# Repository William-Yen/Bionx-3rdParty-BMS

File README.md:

# Bionx-3rdParty-BMS
A supplemental PCB to retrofit a Bionx e-bike battery pack with a 3rd-party BMS

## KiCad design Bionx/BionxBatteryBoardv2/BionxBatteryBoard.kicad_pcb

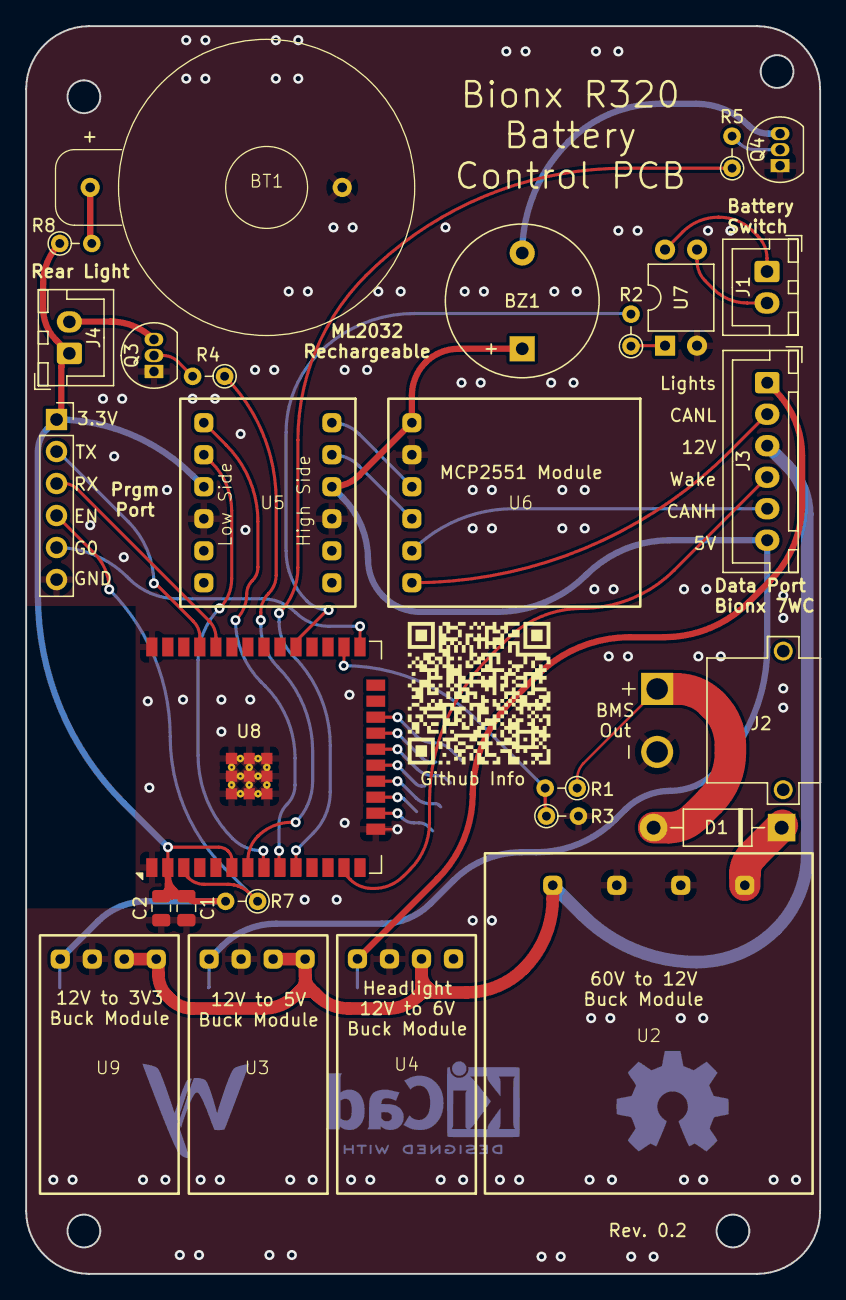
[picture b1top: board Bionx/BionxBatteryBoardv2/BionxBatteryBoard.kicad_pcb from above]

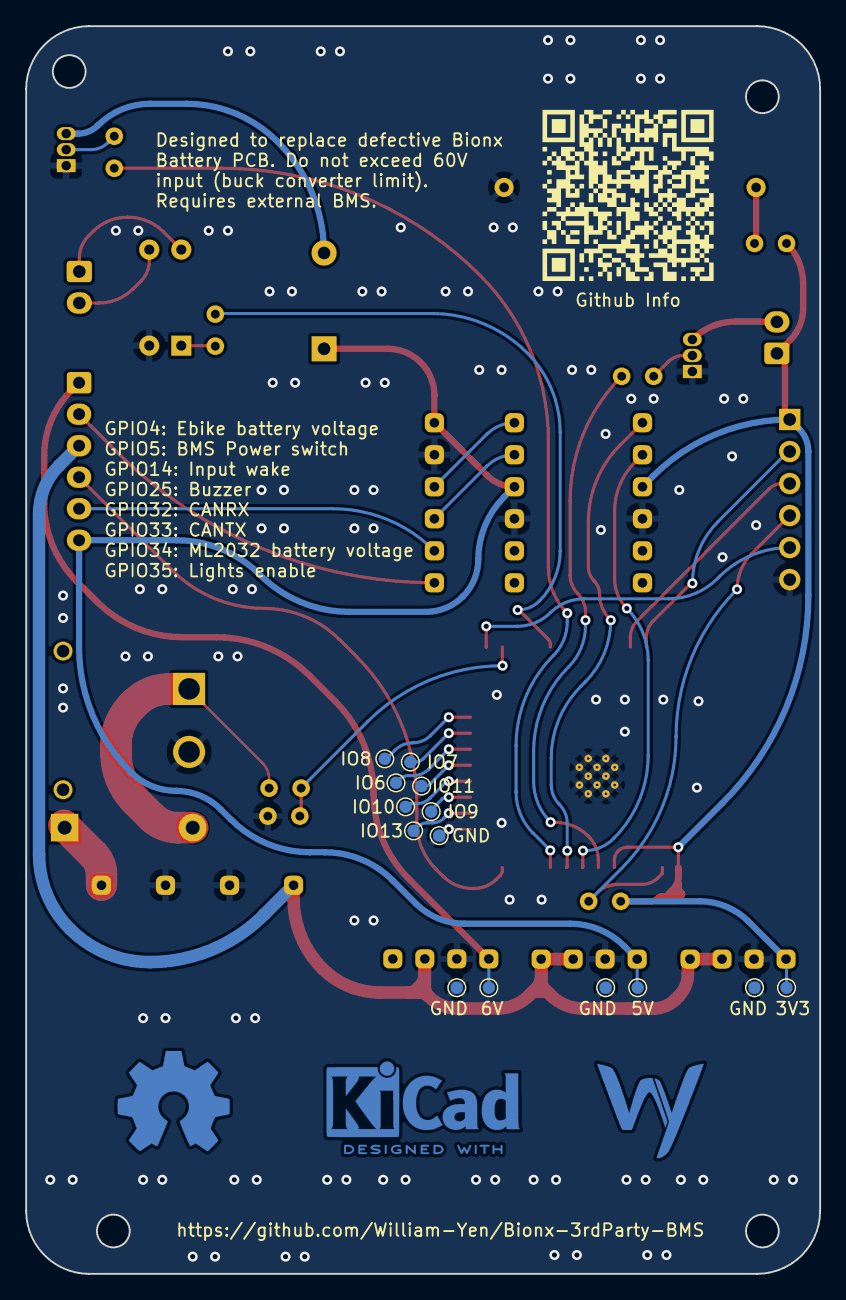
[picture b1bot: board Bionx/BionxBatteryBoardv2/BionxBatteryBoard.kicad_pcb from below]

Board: 2 copper layers, 63.0 x 99.0 mm, 41 parts (14 on the bottom side), 30 nets.

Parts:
3V3, 5V, 6V: TestPoint_Pad_D1.0mm
BT1: Battery_Cell; 2032_THT
BZ1: Buzzer; Buzzer_12x9.5RM7.6
C1: 10uF; C_0805_2012Metric
C2: 100nF; C_0805_2012Metric
D1: D; D_DO-41_SOD81_P10.16mm_Horizontal
GND: TestPoint_Pad_D1.0mm
GND#2, GND#3, GND#4: TestPoint_Pad_D1.0mm
IO6, IO7, IO8, IO9, IO10, IO11, IO13: TestPoint_Pad_D1.0mm
J1, J4: Conn_01x02; JST_XH_B2B-XH-A_1x02_P2.50mm_Vertical
J2: XT30PW-M; AMASS_XT30PW-M
J3: Conn_01x06; JST_XH_B6B-XH-A_1x06_P2.50mm_Vertical
J5: Conn_01x06; PinSocket_1x06_P2.54mm_Vertical
Q3, Q4: 2N3904; TO-92_Inline
R1: 100k; R_Axial_DIN0204_L3.6mm_D1.6mm_P2.54mm_Vertical
R2: 184R; R_Axial_DIN0204_L3.6mm_D1.6mm_P2.54mm_Vertical
R3: 5.1k; R_Axial_DIN0204_L3.6mm_D1.6mm_P2.54mm_Vertical
R4, R5: 220R; R_Axial_DIN0204_L3.6mm_D1.6mm_P2.54mm_Vertical
R7: 10k; R_Axial_DIN0204_L3.6mm_D1.6mm_P2.54mm_Vertical
R8: 680R; R_Axial_DIN0204_L3.6mm_D1.6mm_P2.54mm_Vertical
U2: CR-6030S_Buck_Converter; CR-6030S Buck Module
U3, U4, U9: Adj_Buck_Module; Adj Buck Module
U5: 4-channel_LevelShifter; Logic Level Converter Module
U6: MCP2551_Module; MCP2551 Module
U7: PC817; DIP-4_W7.62mm
U8: ESP32-WROOM-32D; ESP32-WROOM-32E

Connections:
+3.3V: 3V3.1, C1.1, C2.1, J4.1, J5.1, R7.2, R8.1, U5.9 (LV), U8.2 (VDD), U8.6 (IO34), U9.4 (OUT+)
+5V: 5V.1, BZ1.1 (+), J3.6, U3.4 (OUT+), U5.3 (HV), U6.1 (VCC)
+12V: J3.3, U2.4 (OUT+), U3.1 (EN), U3.2 (IN+), U4.2 (IN+), U9.1 (EN), U9.2 (IN+)
+BATT: D1.2 (A), J2.P, R1.1
-BATT: BT1.2 (-), C1.2, C2.2, GND.1, GND#2.1, GND#3.1, GND#4.1, J2.N, J5.6, Q3.1 (E), Q4.1 (E), R3.2, U2.2 (GND), U2.3 (GND), U3.3 (GND), U4.3 (GND), U5.4 (GND), U5.10 (GND), U6.2 (GND), U7.2, U8.1 (GND), U8.15 (GND), U8.38 (GND), U8.39 (GND), U9.3 (GND)
/CAN_H: J3.5, U6.5 (CANH)
/CAN_L: J3.2, U6.6 (CANL)
/CAN_RX: U5.8 (LV2), U8.8 (IO32)
/CAN_TX: U5.7 (LV1), U8.9 (IO33)
/EN: J5.4, R7.1, U8.3 (EN)
/IO0: J5.5, U8.25 (IO0)
/LightsEnable_pin: R4.1, U8.7 (IO35)
/PowerSwitch_pin: R2.2, U8.29 (IO5)
/RX0: J5.3, U8.34 (RXD0/IO3)
/Ride+_Wakepin: J3.4, U8.13 (IO14)
/TX0: J5.2, U8.35 (TXD0/IO1)
/batteryRead_pin: R1.2, R3.1, U8.26 (IO4)
/buzzer_pin: R5.1, U8.10 (IO25)
Headlight_power: 6V.1, J3.1, U4.4 (OUT+)
unnamed: BT1.1 (+), R8.2
unnamed: BZ1.2 (-), Q4.3 (C)
unnamed: D1.1 (K), U2.1 (IN+)
unnamed: J1.1, U7.4
unnamed: J1.2, U7.3
unnamed: J4.2, Q3.3 (C)
unnamed: Q3.2 (B), R4.2
unnamed: Q4.2 (B), R5.2
unnamed: R2.1, U7.1
unnamed: U5.1 (HV1), U6.3 (CTX)
unnamed: U5.2 (HV2), U6.4 (CRX)

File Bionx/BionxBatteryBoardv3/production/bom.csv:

Designator,Footprint,Quantity,Value,LCSC Part #
BT1,2032_THT,1,Battery_Cell,
BZ1,Buzzer_12x9.5RM7.6,1,Buzzer,
C1,0805,1,10uF,
C2,0805,1,100nF,
D1,D_DO-41_SOD81_P10.16mm_Horizontal,1,D,
"J1, J4",JST_XH_B2B-XH-A_1x02_P2.50mm_Vertical,2,Conn_01x02,
J2,AMASS_XT30PW-M,1,XT30PW-M,
J3,JST_XH_B6B-XH-A_1x06_P2.50mm_Vertical,1,Conn_01x06,
J5,PinSocket_1x06_P2.54mm_Vertical,1,Conn_01x06,
"Q3, Q4",TO-92_Inline,2,2N3904,
R1,R_Axial_DIN0204_L3.6mm_D1.6mm_P2.54mm_Vertical,1,100k,
R2,R_Axial_DIN0204_L3.6mm_D1.6mm_P2.54mm_Vertical,1,184R,
R3,R_Axial_DIN0204_L3.6mm_D1.6mm_P2.54mm_Vertical,1,5.1k,
"R4, R5",R_Axial_DIN0204_L3.6mm_D1.6mm_P2.54mm_Vertical,2,220R,
R7,R_Axial_DIN0204_L3.6mm_D1.6mm_P2.54mm_Vertical,1,10k,
R8,R_Axial_DIN0204_L3.6mm_D1.6mm_P2.54mm_Vertical,1,680R,
U2,CR-6030S Buck Module,1,CR-6030S_Buck_Converter,
"U3, U4, U9",Adj Buck Module,3,Adj_Buck_Module,
U5,Logic Level Converter Module,1,4-channel_LevelShifter,
U6,MCP2551 Module,1,MCP2551_Module,
U7,DIP-4_W7.62mm,1,PC817,
U8,ESP32-WROOM-32E,1,ESP32-WROOM-32D,

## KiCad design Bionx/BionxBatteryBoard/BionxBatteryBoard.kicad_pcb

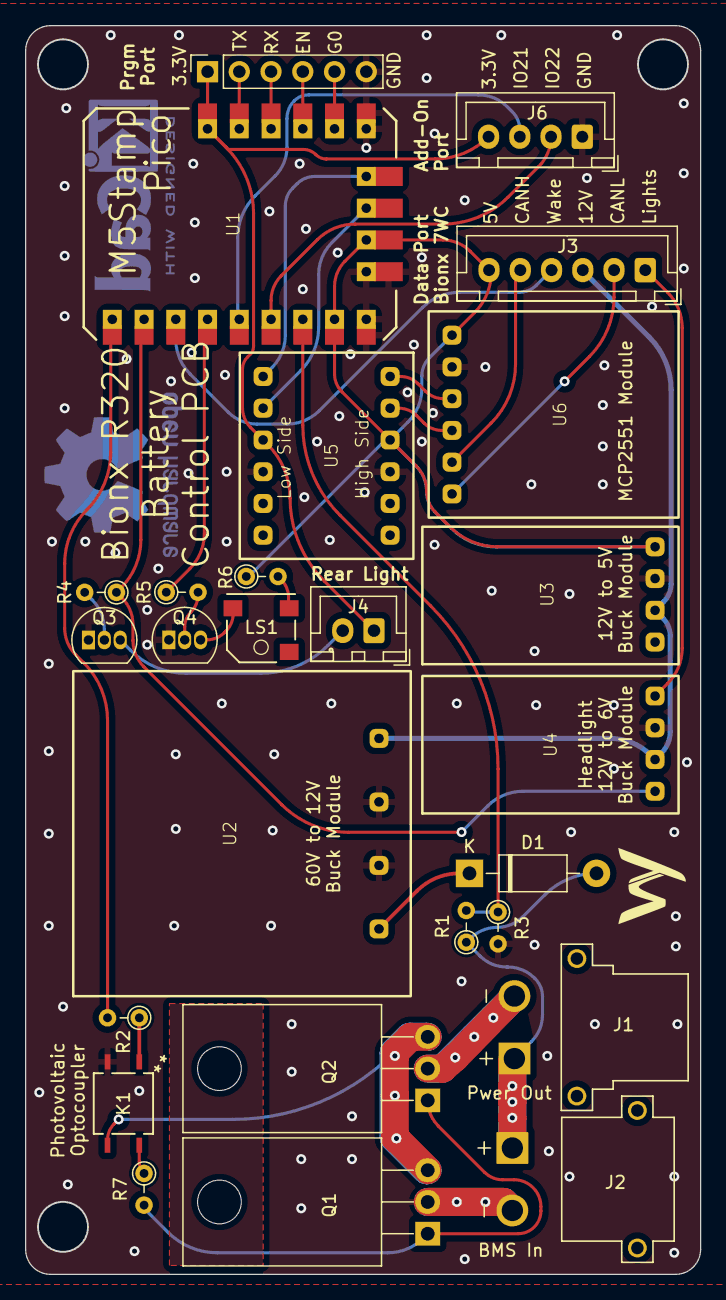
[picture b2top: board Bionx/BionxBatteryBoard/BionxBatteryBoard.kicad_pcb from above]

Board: 2 copper layers, 53.9 x 99.9 mm, 26 parts (0 on the bottom side), 34 nets.

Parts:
D1: D; D_DO-41_SOD81_P10.16mm_Horizontal
J1: XT30PW-F; AMASS_XT30PW-F
J2: XT30PW-M; AMASS_XT30PW-M
J3: Conn_01x06_Socket; JST_XH_B6B-XH-A_1x06_P2.50mm_Vertical
J4: Conn_01x02_Socket; JST_XH_B2B-XH-A_1x02_P2.50mm_Vertical
J5: Conn_01x06_Pin; PinSocket_1x06_P2.54mm_Vertical
J6: Conn_01x04_Socket; JST_XH_B4B-XH-A_1x04_P2.50mm_Vertical
K1: APV1121S; SOP4PIN_PAN
LS1: CMT-0502-75-SMT-TR; CMT-0502_CUD
Q1, Q2: STB75NF75LT4; TO-220-3_Horizontal_TabDown
Q3, Q4: 2N3904; TO-92_Inline
R1, R2, R3, R4, R5, R6, R7: R; R_Axial_DIN0204_L3.6mm_D1.6mm_P2.54mm_Vertical
U1: M5Stack-STAMP-PICO; M5Stamp Pico
U2: CR-6030S_Buck_Converter; CR-6030S Buck Module
U3, U4: Adj_Buck_Module; Adj Buck Module
U5: 4-channel_LevelShifter; Logic Level Converter Module
U6: MCP2551_Module; MCP2551 Module

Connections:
+3.3V: J4.1, J5.1, J6.4, U1.19 (3V3), U5.9 (LV)
+5V: J3.6, R6.1, U1.8 (5V), U1.11 (5V), U3.4 (OUT+), U5.3 (HV), U6.1 (VCC)
+12V: J3.3, U2.4 (OUT+), U3.2 (IN+), U4.2 (IN+)
+BATT: D1.2 (A), J1.P, J2.P, R1.1
-BATT: J2.N, J5.6, J6.1, K1.2, Q1.2 (D), Q3.1 (E), Q4.1 (E), R3.2, U1.9 (GND), U1.10 (GND), U1.14 (GND), U2.2 (GND), U2.3 (GND), U3.3 (GND), U4.3 (GND), U5.4 (GND), U5.10 (GND), U6.2 (GND)
-OUT: J1.N, Q2.2 (D)
/BMS_RX: J6.2, U1.6 (G22)
/BMS_TX: J6.3, U1.5 (G21)
/CAN_H: J3.5, U6.5 (CANH)
/CAN_L: J3.2, U6.6 (CANL)
/CAN_RX: U1.12 (G32), U5.8 (LV2)
/CAN_TX: U1.13 (G33), U5.7 (LV1)
/Headlight_power: J3.1, U4.4 (OUT+)
/LightsEnable_pin: R4.1, U1.2 (G36), U4.1 (EN)
/PowerSwitch_pin: R2.2, U1.1 (G26)
/Ride+_Wakepin: J3.4, U1.3 (G18)
/batteryRead_pin: R1.2, R3.1, U1.7 (G25)
/buzzer_pin: R5.1, U1.4 (G19)
Drain: K1.3, Q1.3 (S), Q2.3 (S)
unnamed: D1.1 (K), U2.1 (IN+)
unnamed: J4.2, Q3.3 (C)
unnamed: J5.2, U1.18 (G1/Tx0)
unnamed: J5.3, U1.17 (G3/Rx0)
unnamed: J5.4, U1.16 (EN)
unnamed: J5.5, U1.15 (G0)
unnamed: K1.1, R2.1
unnamed: K1.4, R7.1
unnamed: LS1.1 (+), R6.2
unnamed: LS1.2 (-), Q4.3 (C)
unnamed: Q1.1 (G), Q2.1 (G), R7.2
unnamed: Q3.2 (B), R4.2
unnamed: Q4.2 (B), R5.2
unnamed: U5.1 (HV1), U6.3 (CTX)
unnamed: U5.2 (HV2), U6.4 (CRX)

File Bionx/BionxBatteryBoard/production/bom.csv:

Designator,Footprint,Quantity,Value,LCSC Part #
D1,D_DO-41_SOD81_P10.16mm_Horizontal,1,D,
J1,AMASS_XT30PW-F,1,XT30PW-F,
J2,AMASS_XT30PW-M,1,XT30PW-M,
J3,JST_XH_B6B-XH-A_1x06_P2.50mm_Vertical,1,Conn_01x06_Socket,
J4,JST_XH_B2B-XH-A_1x02_P2.50mm_Vertical,1,Conn_01x02_Socket,
J5,PinSocket_1x06_P2.54mm_Vertical,1,Conn_01x06_Pin,
J6,JST_XH_B4B-XH-A_1x04_P2.50mm_Vertical,1,Conn_01x04_Socket,
K1,SOP4PIN_PAN,1,APV1121S,
LS1,CMT-0502_CUD,1,CMT-0502-75-SMT-TR,
"Q1, Q2",TO-220-3_Horizontal_TabDown,2,STB75NF75LT4,
"Q3, Q4",TO-92_Inline,2,2N3904,
"R1, R2, R3, R4, R5, R6, R7",R_Axial_DIN0204_L3.6mm_D1.6mm_P2.54mm_Vertical,7,R,
U1,M5Stamp Pico,1,M5Stack-STAMP-PICO,
U2,CR-6030S Buck Module,1,CR-6030S_Buck_Converter,
"U3, U4",Adj Buck Module,2,Adj_Buck_Module,
U5,Logic Level Converter Module,1,4-channel_LevelShifter,
U6,MCP2551 Module,1,MCP2551_Module,

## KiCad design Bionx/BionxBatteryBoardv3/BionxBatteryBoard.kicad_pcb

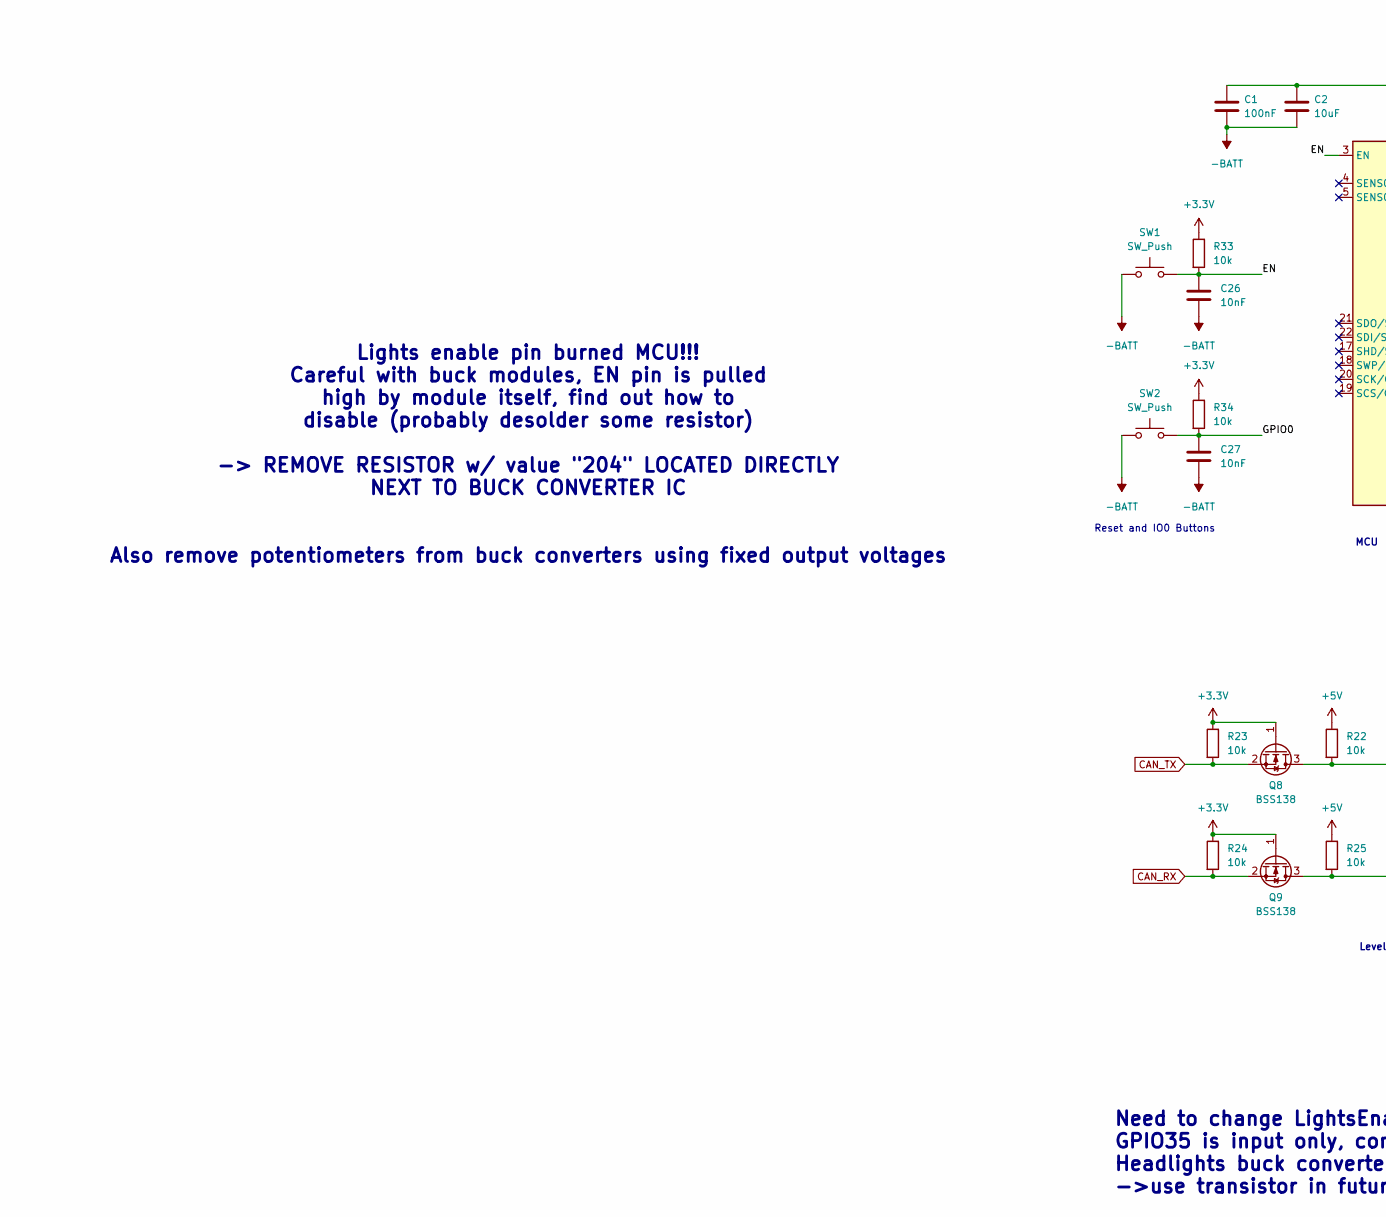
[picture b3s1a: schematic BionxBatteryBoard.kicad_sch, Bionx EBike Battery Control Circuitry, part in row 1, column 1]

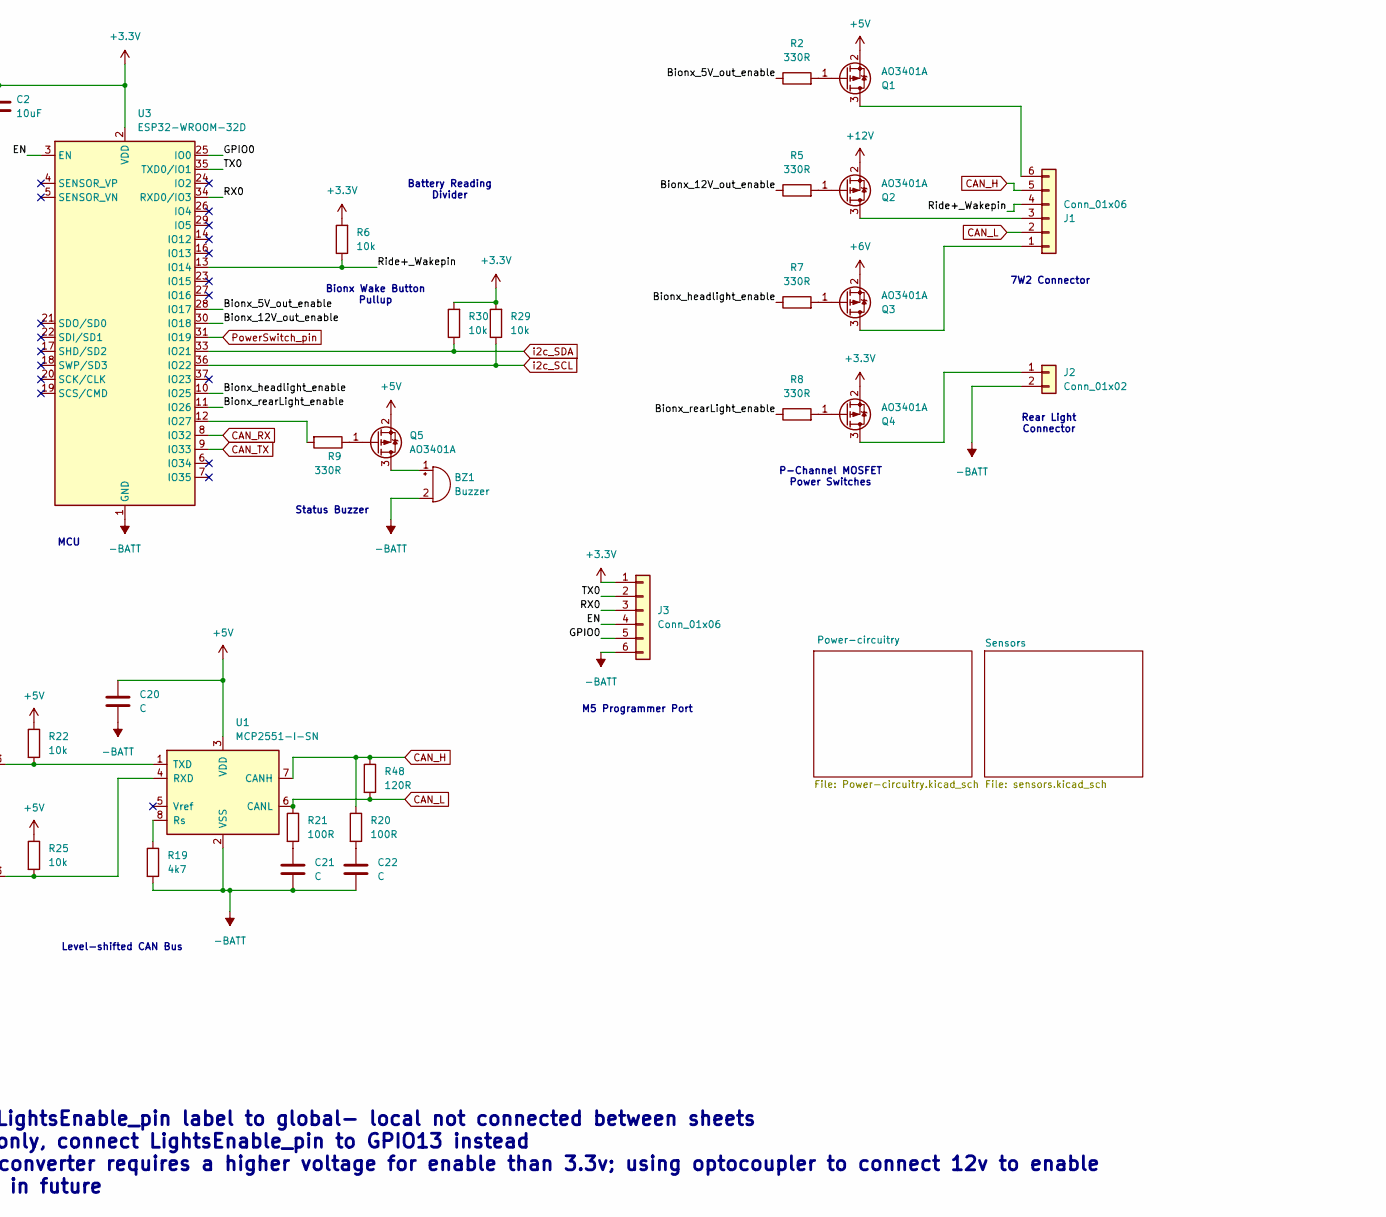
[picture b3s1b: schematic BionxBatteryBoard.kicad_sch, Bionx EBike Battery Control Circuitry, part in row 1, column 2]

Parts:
BZ1: Buzzer; Buzzer_12x9.5RM7.6
C1: 100nF; C_0805_2012Metric
C2: 10uF; C_0805_2012Metric
C20, C21, C22: C; C_0603_1608Metric
C26, C27: 10nF; C_0402_1005Metric
J1: Conn_01x06; JST_XH_S6B-XH-A_1x06_P2.50mm_Horizontal
J2: Conn_01x02; JST_XH_B2B-XH-A_1x02_P2.50mm_Vertical
J3: Conn_01x06; PinHeader_1x06_P2.54mm_Vertical
Q1, Q2, Q3, Q4, Q5: AO3401A; SOT-23
Q8, Q9: BSS138; SOT-23
R2, R5, R7, R8, R9: 330R; R_0402_1005Metric
R6, R22, R23, R24, R25, R29, R30, R33, R34: 10k; R_0402_1005Metric
R19: 4k7; R_0603_1608Metric
R20, R21: 100R; R_0603_1608Metric
R48: 120R; R_0402_1005Metric
SW1, SW2: SW_Push; G-Switch 3.9x3mm
U1: MCP2551-I-SN; SOIC-8_3.9x4.9mm_P1.27mm
U3: ESP32-WROOM-32D

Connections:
+3.3V: C1.1, C2.1, J3.1, Q4.2 (S), Q8.1 (G), Q9.1 (G), R6.2, R23.1, R24.1, R29.2, R30.2, R33.1, R34.1, U3.2 (VDD); also elsewhere on the board
+5V: C20.1, Q1.2 (S), Q5.2 (S), R22.1, R25.1, U1.3 (VDD); also elsewhere on the board
+6V: Q3.2 (S); also elsewhere on the board
+12V: Q2.2 (S); also elsewhere on the board
-BATT: BZ1.2 (-), C1.2, C2.2, C20.2, C21.2, C22.2, C26.2, C27.2, J2.2, J3.6, R19.2, SW1.1, SW2.1, U1.2 (VSS), U3.1 (GND), U3.15 (GND), U3.38 (GND), U3.39 (GND); also elsewhere on the board
/Bionx_5V_out_enable: R2.1, U3.28 (IO17)
/Bionx_12V_out_enable: R5.1, U3.30 (IO18)
/Bionx_headlight_enable: R7.1, U3.10 (IO25)
/Bionx_rearLight_enable: R8.1, U3.11 (IO26)
/EN: C26.1, J3.4, R33.2, SW1.2, U3.3 (EN)
/GPIO0: C27.1, J3.5, R34.2, SW2.2, U3.25 (IO0)
/RX0: J3.3, U3.34 (RXD0/IO3)
/Ride+_Wakepin: J1.4, R6.1, U3.13 (IO14)
/TX0: J3.2, U3.35 (TXD0/IO1)
CAN_H: J1.5, R20.1, R48.1, U1.7 (CANH); also elsewhere on the board
CAN_L: J1.2, R21.1, R48.2, U1.6 (CANL); also elsewhere on the board
CAN_RX: Q9.2 (S), R24.2, U3.8 (IO32)
CAN_TX: Q8.2 (S), R23.2, U3.9 (IO33)
unnamed: BZ1.1 (+), Q5.3 (D)
unnamed: C21.1, R21.2
unnamed: C22.1, R20.2
unnamed: J1.1, Q3.3 (D)
unnamed: J1.3, Q2.3 (D)
unnamed: J1.6, Q1.3 (D)
unnamed: J2.1, Q4.3 (D)
unnamed: Q1.1 (G), R2.2
unnamed: Q2.1 (G), R5.2
unnamed: Q3.1 (G), R7.2
unnamed: Q4.1 (G), R8.2
unnamed: Q5.1 (G), R9.1
unnamed: Q8.3 (D), R22.2, U1.1 (TXD)
unnamed: Q9.3 (D), R25.2, U1.4 (RXD)
unnamed: R19.1, U1.8 (Rs)
unnamed: R9.2, U3.12 (IO27)
PowerSwitch_pin: U3.31 (IO19); also elsewhere on the board
i2c_SCL: R29.1, U3.36 (IO22); also elsewhere on the board
i2c_SDA: R30.1, U3.33 (IO21); also elsewhere on the board

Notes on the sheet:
P-Channel MOSFET Power Switches
Level-shifted CAN Bus
MCU
Need to change LightsEnable_pin label to global- local not connected between sheets GPIO35 is input only, connect LightsEnable_pin to GPIO13 instead Headlights buck converter requires a higher voltage for enable than 3.3v; using optocoupler to connect 12v to enable ->use transistor in future
Status Buzzer
Reset and IO0 Buttons
M5 Programmer Port
Battery Reading Divider
7W2 Connector
Lights enable pin burned MCU!!! Careful with buck modules, EN pin is pulled high by module itself, find out how to disable (probably desolder some resistor) -> REMOVE RESISTOR w/ value "204" LOCATED DIRECTLY NEXT TO BUCK CONVERTER IC Also remove potentiometers from buck converters using fixed outpu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
Rear Light Connector
Bionx Wake Button Pullup

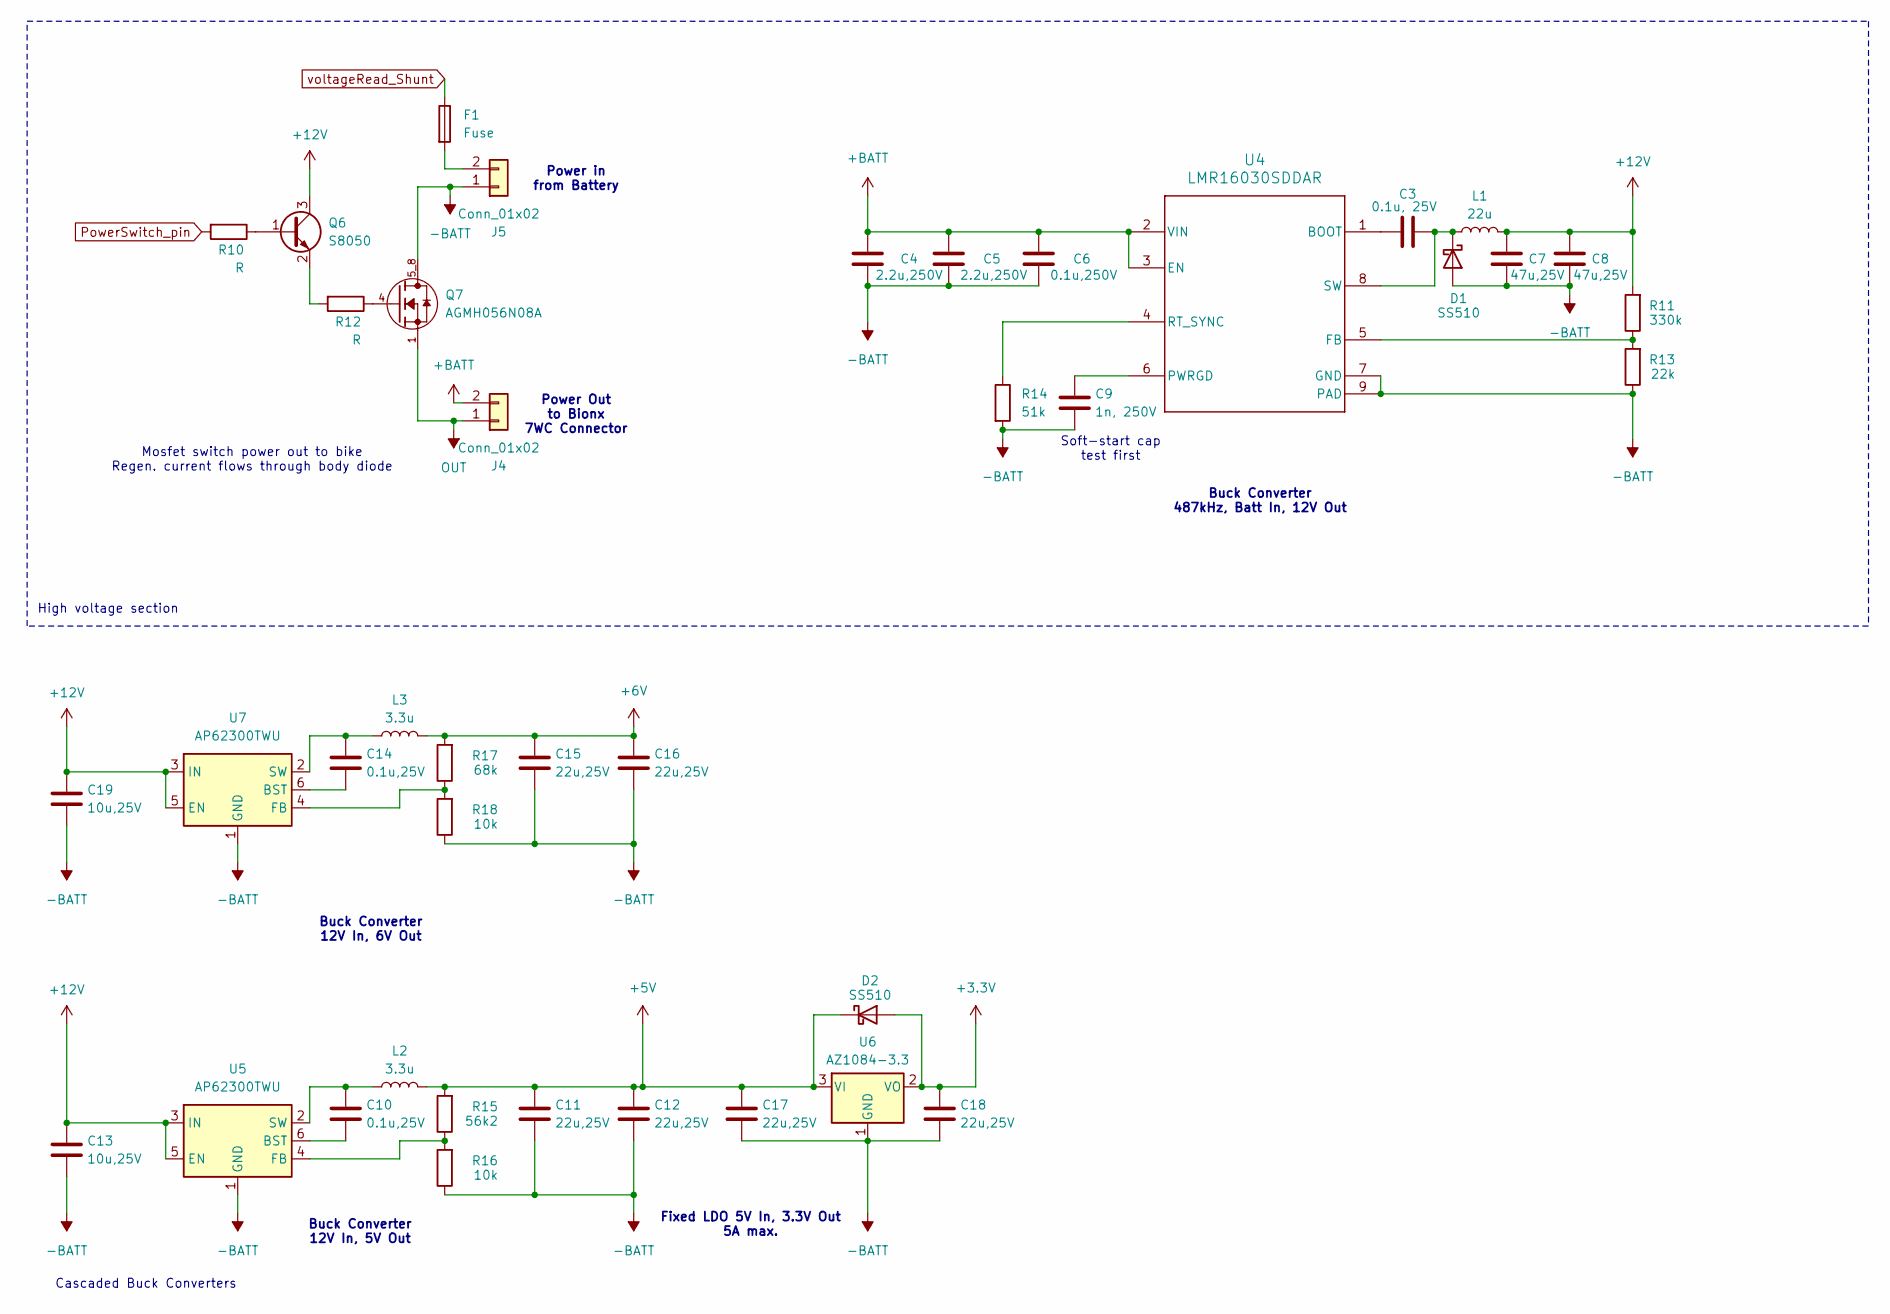
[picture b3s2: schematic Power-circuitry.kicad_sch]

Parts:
C3: 0.1u, 25V; C_0402_1005Metric
C4, C5: 2.2u,250V; C_2220_5750Metric
C6: 0.1u,250V; C_1206_3216Metric
C7, C8: 47u,25V; C_1206_3216Metric
C9: 1n, 250V; C_0603_1608Metric
C10, C14: 0.1u,25V; C_0402_1005Metric
C11, C12, C15, C16, C17, C18: 22u,25V; C_0805_2012Metric
C13, C19: 10u,25V; C_0805_2012Metric
D1, D2: SS510; D_SMA
F1: Fuse; Fuseholder_Blade_Mini_Keystone_3568
J4: Conn_01x02; AMASS_XT30PW-F_1x02_P2.50mm_Horizontal
J5: Conn_01x02; AMASS_XT30PW-M_1x02_P2.50mm_Horizontal
L1: 22u; L_Chilisin_BMRF00101040
L2, L3: 3.3u; L_Chilisin_BMRx00040412
Q6: S8050; SOT-23
Q7: AGMH056N08A; PARTREV A1910
R10, R12: R; R_0402_1005Metric
R11: 330k; R_0603_1608Metric
R13: 22k; R_0603_1608Metric
R14: 51k; R_0603_1608Metric
R15: 56k2; R_0402_1005Metric
R16, R18: 10k; R_0402_1005Metric
R17: 68k; R_0402_1005Metric
U4: LMR16030SDDAR; DDA0008E_N
U5, U7: AP62300TWU; TSOT-23-6
U6: AZ1084-3.3; TO-252-2

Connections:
+3.3V: C18.1, D2.2 (A), U6.2 (VO); also elsewhere on the board
+5V: C11.1, C12.1, C17.1, D2.1 (K), L2.2, R15.2, U6.3 (VI); also elsewhere on the board
+6V: C15.1, C16.1, L3.2, R17.2; also elsewhere on the board
+12V: C7.2, C8.2, C13.1, C19.1, L1.2, Q6.3 (C), R11.2, U5.3 (IN), U5.5 (EN), U7.3 (IN), U7.5 (EN); also elsewhere on the board
+BATT: C4.2, C5.2, C6.2, J4.2, U4.2 (VIN), U4.3 (EN); also elsewhere on the board
-BATT: C4.1, C5.1, C6.1, C7.1, C8.1, C9.2, C11.2, C12.2, C13.2, C15.2, C16.2, C17.2, C18.2, C19.2, D1.2 (A), J5.1, Q7.5_8, R13.1, R14.2, R16.1, R18.1, U4.7 (GND), U4.9 (PAD), U5.1 (GND), U6.1 (GND), U7.1 (GND); also elsewhere on the board
unnamed: C3.2, D1.1 (K), L1.1, U4.8 (SW)
unnamed: F1.2, J5.2
unnamed: Q6.1 (B), R10.1
unnamed: Q6.2 (E), R12.2
unnamed: Q7.4, R12.1
unnamed: C3.1, U4.1 (BOOT)
unnamed: R11.1, R13.2, U4.5 (FB)
unnamed: C9.1, U4.6 (PWRGD)
unnamed: R14.1, U4.4 (RT_SYNC)
unnamed: C10.2, U5.6 (BST)
unnamed: R15.1, R16.2, U5.4 (FB)
unnamed: C10.1, L2.1, U5.2 (SW)
unnamed: C14.2, U7.6 (BST)
unnamed: R17.1, R18.2, U7.4 (FB)
unnamed: C14.1, L3.1, U7.2 (SW)
OUT: J4.1, Q7.1, Q7.2, Q7.3
PowerSwitch_pin: R10.2; also elsewhere on the board
voltageRead_Shunt: F1.1; also elsewhere on the board

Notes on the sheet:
Cascaded Buck Converters
Buck Converter 12V In, 6V Out
Fixed LDO 5V In, 3.3V Out 5A max.
Buck Converter 487kHz, Batt In, 12V Out
High voltage section
Power in from Battery
Soft-start cap test first
Power Out to Bionx 7WC Connector
Buck Converter 12V In, 5V Out
Mosfet switch power out to bike Regen. current flows through body diode

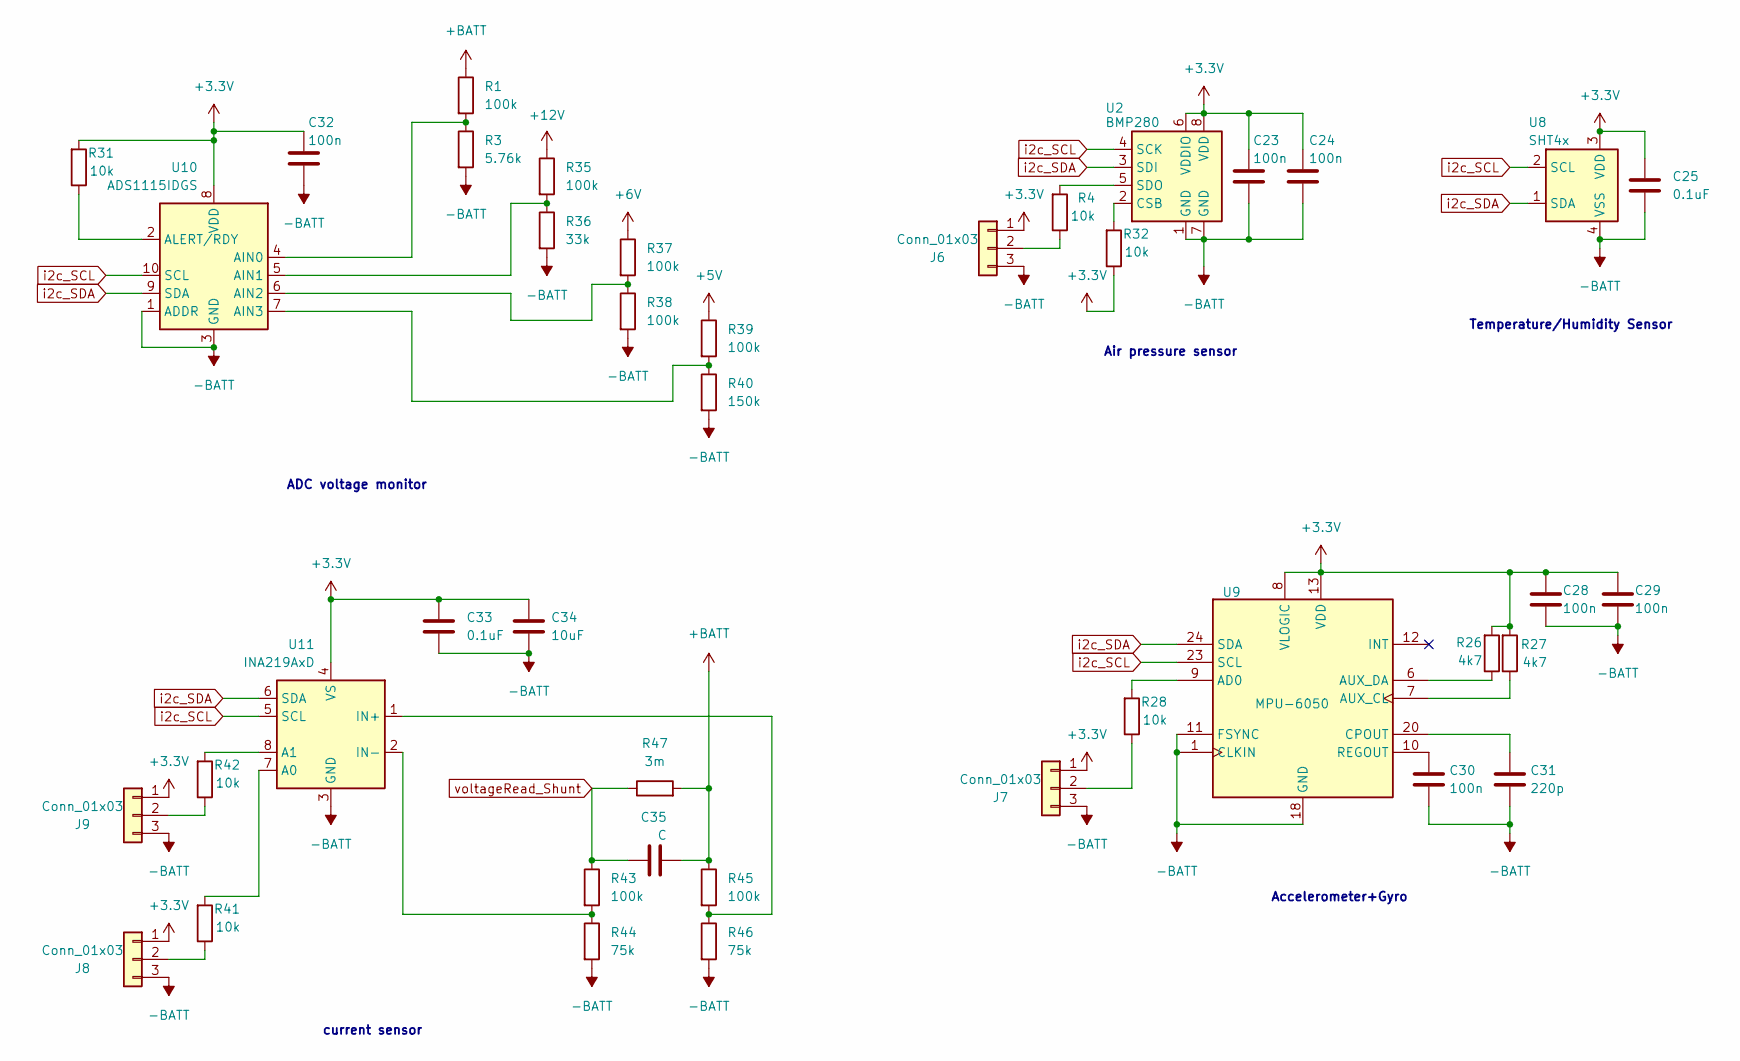
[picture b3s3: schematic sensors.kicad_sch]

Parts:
C23, C24, C28, C29, C30, C32: 100n; C_0603_1608Metric
C25, C33: 0.1uF; C_0402_1005Metric
C31: 220p; C_0603_1608Metric
C34: 10uF; C_0805_2012Metric
C35: C; C_0603_1608Metric
J6, J7, J8, J9: Conn_01x03; bridgePads_3_1mm
R1, R35, R37, R38, R39, R43, R45: 100k; R_0603_1608Metric
R3: 5.76k; R_0603_1608Metric
R4, R28, R31, R32, R41, R42: 10k; R_0402_1005Metric
R26, R27: 4k7; R_0402_1005Metric
R36: 33k; R_0603_1608Metric
R40: 150k; R_0603_1608Metric
R44, R46: 75k; R_0603_1608Metric
R47: 3m; R_2512_6332Metric
U2: BMP280; Bosch_LGA-8_2x2.5mm_P0.65mm_ClockwisePinNumbering
U8: SHT4x; Sensirion_DFN-4_1.5x1.5mm_P0.8mm_SHT4x_NoCentralPad
U9: MPU-6050; InvenSense_QFN-24_4x4mm_P0.5mm
U10: ADS1115IDGS; TSSOP-10_3x3mm_P0.5mm
U11: INA219AxD; SOT-23-8

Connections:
+3.3V: C23.1, C24.1, C25.1, C28.1, C29.1, C32.1, C33.1, C34.1, J6.1, J7.1, J8.1, J9.1, R26.2, R27.2, R31.2, R32.1, U2.6 (VDDIO), U2.8 (VDD), U8.3 (VDD), U9.8 (VLOGIC), U9.13 (VDD), U10.8 (VDD), U11.4 (VS); also elsewhere on the board
+5V: R39.1; also elsewhere on the board
+6V: R37.1; also elsewhere on the board
+12V: R35.1; also elsewhere on the board
+BATT: C35.2, R1.1, R45.1, R47.2; also elsewhere on the board
-BATT: C23.2, C24.2, C25.2, C28.2, C29.2, C30.2, C31.2, C32.2, C33.2, C34.2, J6.3, J7.3, J8.3, J9.3, R3.2, R36.2, R38.2, R40.2, R44.2, R46.2, U2.1 (GND), U2.7 (GND), U8.4 (VSS), U9.1 (CLKIN), U9.11 (FSYNC), U9.18 (GND), U10.1 (ADDR), U10.3 (GND), U11.3 (GND); also elsewhere on the board
unnamed: J6.2, R4.1
unnamed: J7.2, R28.1
unnamed: J8.2, R41.1
unnamed: J9.2, R42.1
unnamed: R32.2, U2.2 (CSB)
unnamed: R4.2, U2.5 (SDO)
unnamed: R28.2, U9.9 (AD0)
unnamed: R27.1, U9.7 (AUX_CL)
unnamed: R26.1, U9.6 (AUX_DA)
unnamed: C31.1, U9.20 (CPOUT)
unnamed: C30.1, U9.10 (REGOUT)
unnamed: R1.2, R3.1, U10.4 (AIN0)
unnamed: R35.2, R36.1, U10.5 (AIN1)
unnamed: R37.2, R38.1, U10.6 (AIN2)
unnamed: R39.2, R40.1, U10.7 (AIN3)
unnamed: R31.1, U10.2 (ALERT/RDY)
unnamed: R41.2, U11.7 (A0)
unnamed: R42.2, U11.8 (A1)
unnamed: R45.2, R46.1, U11.1 (IN+)
unnamed: R43.2, R44.1, U11.2 (IN-)
i2c_SCL: U2.4 (SCK), U8.2 (SCL), U9.23 (SCL), U10.10 (SCL), U11.5 (SCL); also elsewhere on the board
i2c_SDA: U2.3 (SDI), U8.1 (SDA), U9.24 (SDA), U10.9 (SDA), U11.6 (SDA); also elsewhere on the board
voltageRead_Shunt: C35.1, R43.1, R47.1; also elsewhere on the board

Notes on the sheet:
ADC voltage monitor
Air pressure sensor
Accelerometer+Gyro
Temperature/Humidity Sensor
current sensor

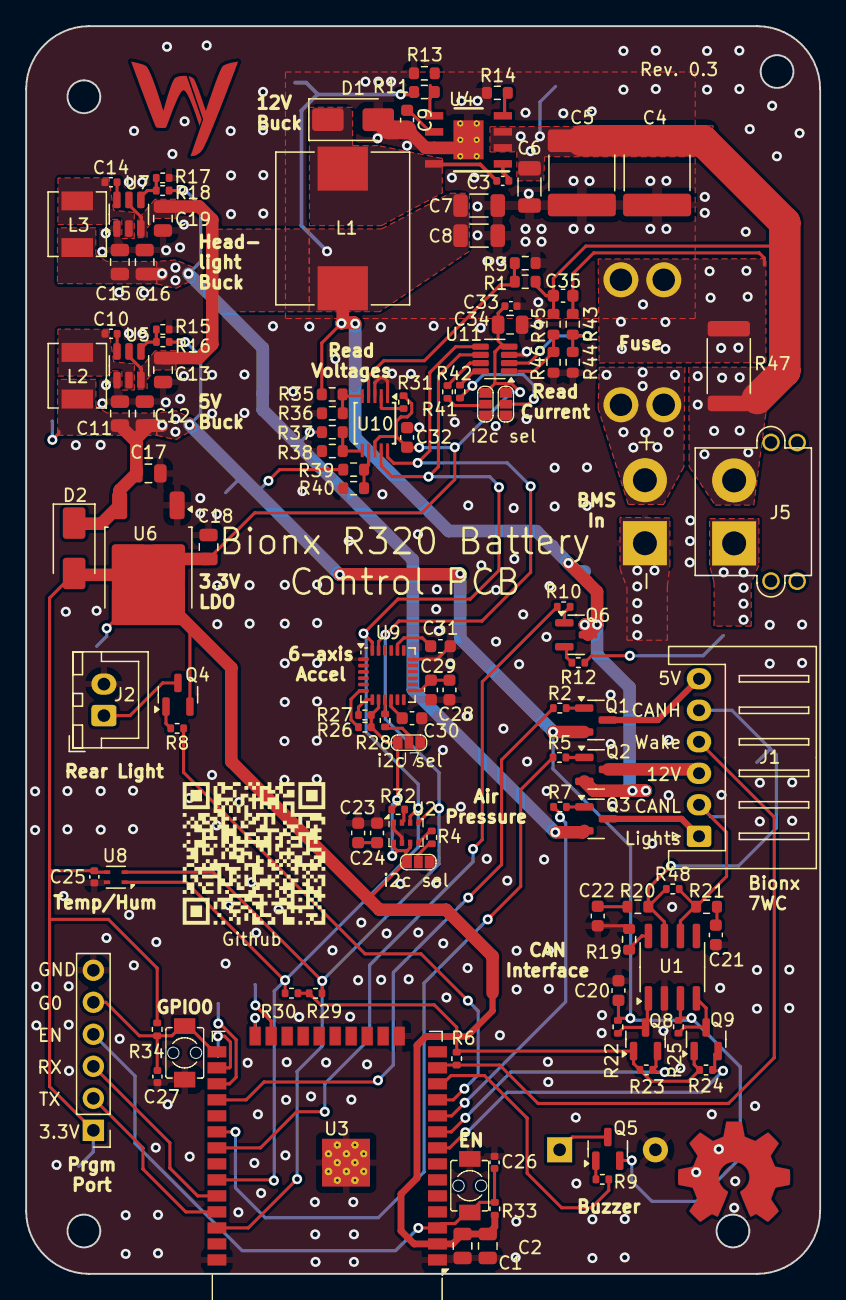
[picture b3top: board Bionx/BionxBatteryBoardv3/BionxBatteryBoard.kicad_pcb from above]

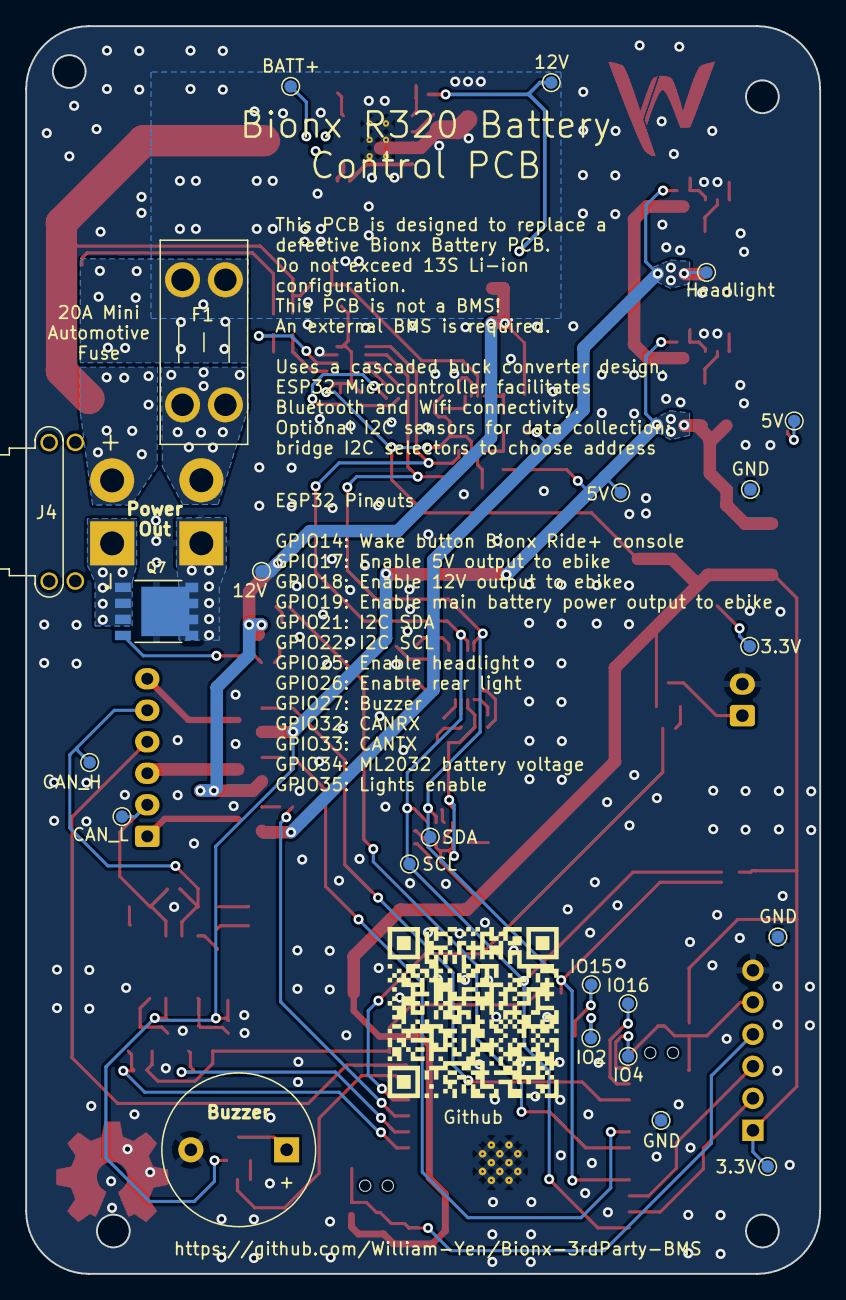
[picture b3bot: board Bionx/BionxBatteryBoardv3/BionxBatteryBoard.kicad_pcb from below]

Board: 2 copper layers, 63.0 x 99.0 mm, 140 parts (23 on the bottom side), 75 nets.

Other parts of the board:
3.3V, 3.3V#2, 5V, 5V#2, 12V, 12V#2: TestPoint_Pad_D1.0mm
BATT+: TestPoint_Pad_D1.0mm
CAN_H: TestPoint_Pad_D1.0mm
CAN_L: TestPoint_Pad_D1.0mm
GND: TestPoint_Pad_D1.0mm
GND#2, GND#3: TestPoint_Pad_D1.0mm
Headlight: TestPoint_Pad_D1.0mm
IO2, IO4, IO15, IO16: TestPoint_Pad_D1.0mm
SCL: TestPoint_Pad_D1.0mm
SDA: TestPoint_Pad_D1.0mm

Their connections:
+3.3V: 3.3V.1, 3.3V#2.1; also elsewhere on the board
+5V: 5V.1, 5V#2.1; also elsewhere on the board
+6V: Headlight.1; also elsewhere on the board
+12V: 12V.1, 12V#2.1; also elsewhere on the board
+BATT: BATT+.1; also elsewhere on the board
-BATT: GND.1, GND#2.1, GND#3.1; also elsewhere on the board
CAN_H: CAN_H.1; also elsewhere on the board
CAN_L: CAN_L.1; also elsewhere on the board
i2c_SCL: SCL.1; also elsewhere on the board
i2c_SDA: SDA.1; also elsewhere on the board

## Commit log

2024-12-21 Dump of first 3 board revisions
    BionxBatteryBoardv3 is most current; has not been manufactured/tested yet.
